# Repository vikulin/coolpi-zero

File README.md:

# GammaPi Zero - The portable FPGA development board

## What is the GammaPi Zero?

The GammaPi Zero is an FPGA development board in the popular Raspberry Pi Zero form factor inheriting Icepi Zero board. It carries a Lattice ECP5 25F, enabling powerful designs while keeping a small portable size. It also has a GPDI mini (General Purpose Display Interface, same as the one on the Pi Zero) port allowing easy digital video output.

## Why GammaPi Zero?

Currently most powerful FPGA boards on the market are expensive and bulky.

I've always wanted a low-cost portable FPGA with video output to make my own CPU, but there isn't any on the market.

The GammaPi Zero aims to fix this. Carrying a powerful ECP5 FPGA on a small Raspberry Pi Zero form factor, it is the ultimate portable solution for FPGA development. Additionally packing a GPDI mini port and 3 USB-C ports, it allows interfacing with multiple external I/O devGammas.

GammaPi Zero is for everyone: Students can use it to learn about the internals of modern processors. Gamers can use it to emulate old hardware. Programmers can use it to test their code on multiple architectures.

GammaPi Zero also has an on-board USB to JTAG converter, so no external programmers are needed.

Moreover GammaPi Zero is fully open-source, no strings attached. Learn from the design! ([OSHWA cerified FR000026](https://certification.oshwa.org/fr000026.html)).

## Features
    * Lattice ECP5U-25F-CABGA256 FPGA
    * 256 Mib SDRAM
    * DVI video output via HDMI connector
    * 50 MBPS ADC
    * 3× USB ports (1× programming/JTAG, 2× general purpose)
    * USB-JTAG programming interface
    * Mini SD card reader
    * 5× RGB LEDs
    * 2× user buttons
    * RP Zero–compatible pins and board size
    * Board dimensions: 65 × 30 mm

This powerful configuration allows the PCB to be used in numerous ways, including real time video processing, hardware AI acceleration and prototyping of ASICs. 

## Emulation

Over the course of multiple weeks, multiple emulation cores have been ported over, such as the [Oberon](https://github.com/cheyao/oberon), [Apple I](https://github.com/cheyao/apple-one) and the [Acorn Atom](https://github.com/cheyao/acorn_atom)! The GammaPi Zero allows you to take cycle accurate replicas of your favourite systems in your pocket.

## Learning

It is also supported by Icestudio (custom fork: https://github.com/cheyao/Icestudio), allowing easy access for beginners.

## Usage

Check out the `firmware` folder for example code and compilation instructions!

If you want to order this board, it uses a 1.2mm/1.6mm PCB with JLC04121H-7628 Stackup. Gerbers are in the `production` folder in the `hardware` directory.

For the PCB, the smallest component size is 0201 for 27 Ohm resistors on the USB-C datalines. But if you want only 0402 components, just delete those 0201 resistors and you will be fine.

NOTE: If you fabbed v1.1 before 01/06, the pins of the USB pullups and LED0 is different - check your gerbers.

## Contact

If there is any questions email me `vadym.vikulin _at_ gmail.com` or DM `@Cyao` on Hackclub Slack.

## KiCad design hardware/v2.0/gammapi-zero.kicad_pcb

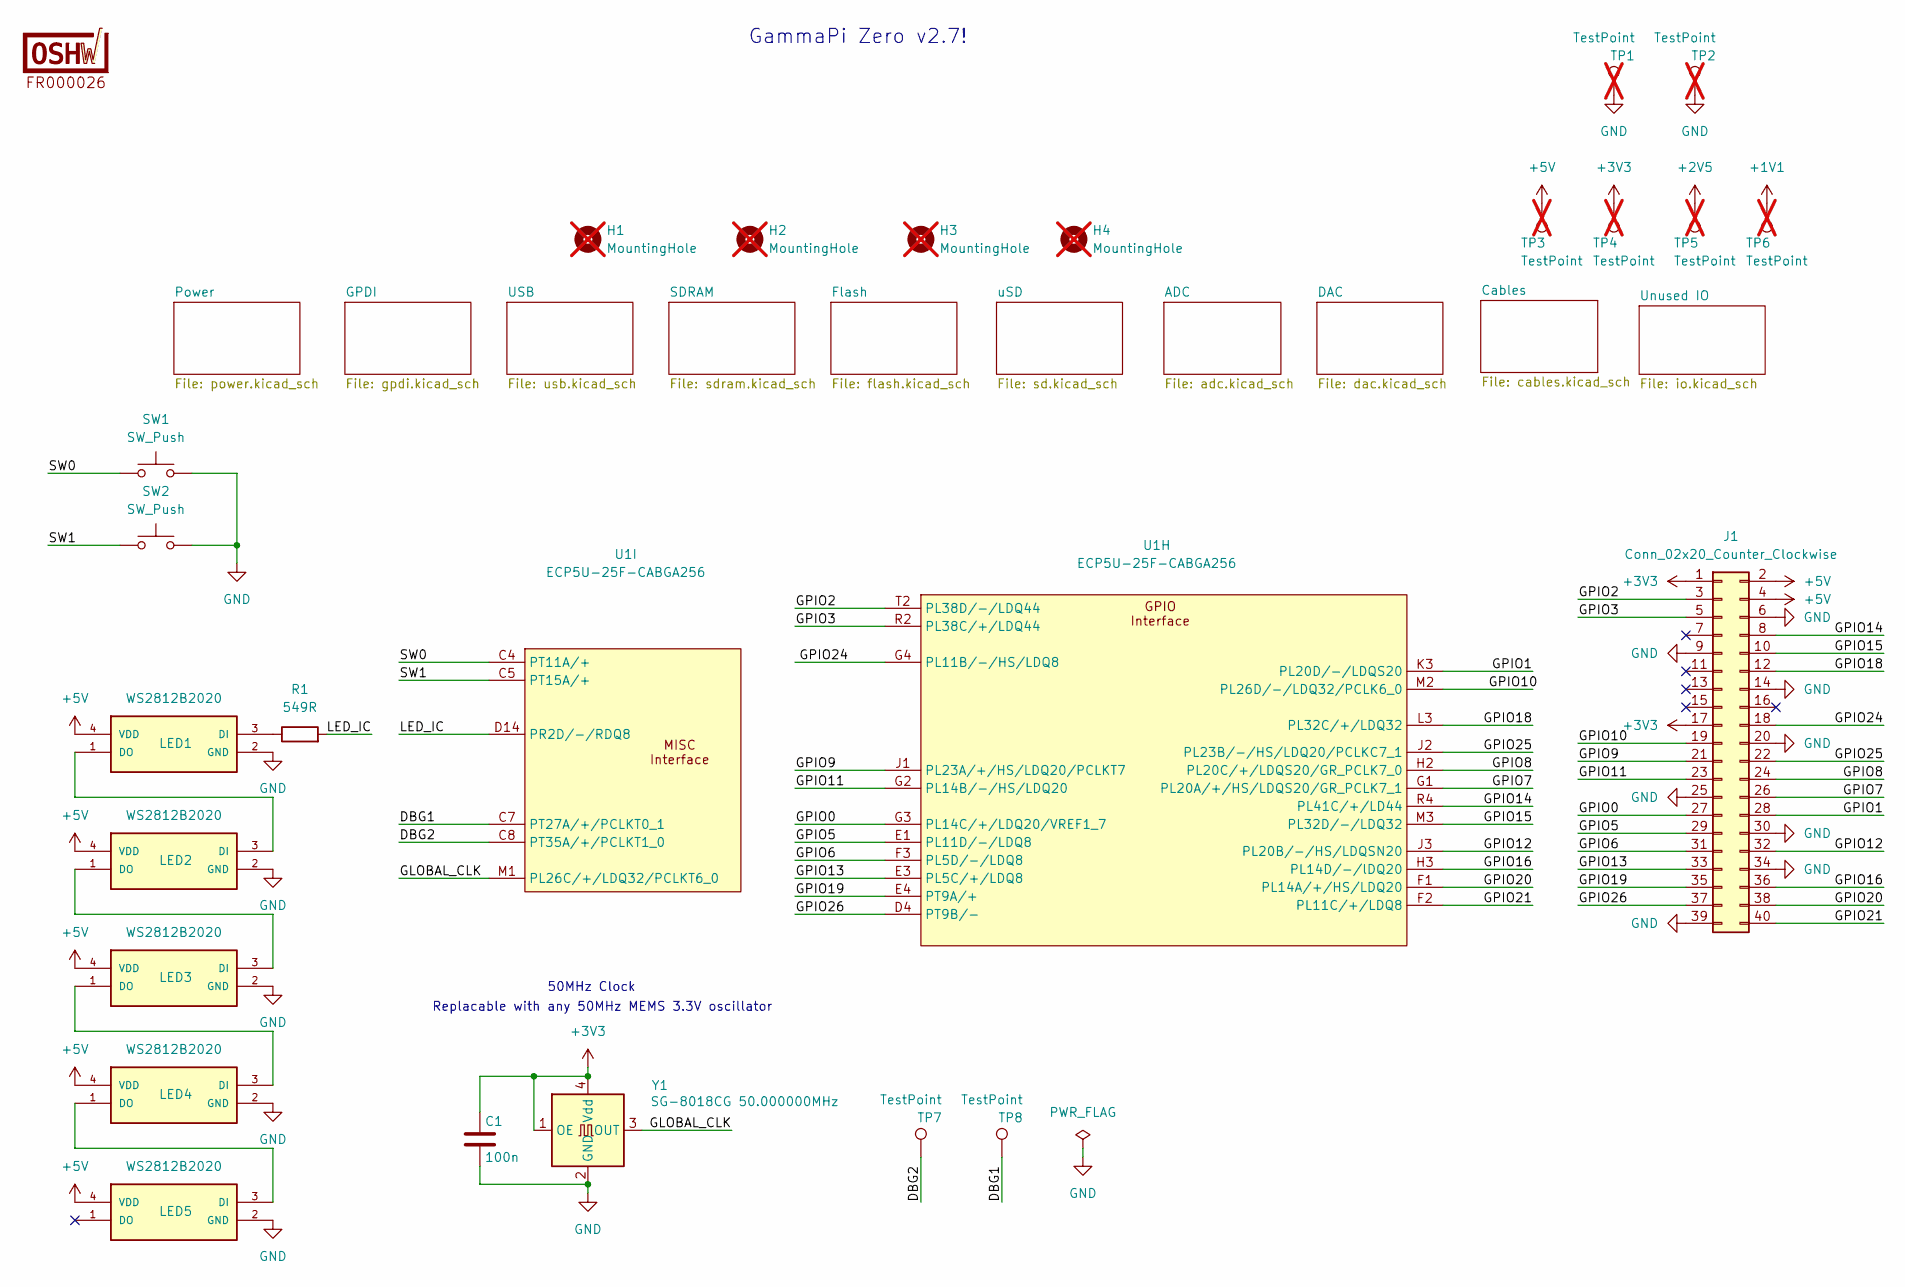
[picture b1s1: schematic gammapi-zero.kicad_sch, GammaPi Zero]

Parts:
C1: 100n; C_0402_1005Metric; Manufactuer Part Number CL05B104KB54PNC; LCSC Part # C307331
H1, H2, H3, H4: MountingHole; MountingHole_2.7mm_M2.5; not fitted
J1: Conn_02x20_Counter_Clockwise; PinHeader_2x20_P2.54mm_Vertical
LED1, LED2, LED3, LED4, LED5: WS2812B2020; LED_WS2812B2020; PARTREV V1.0; LCSC Part # C965555
LOGO1: OSHW-Certification-Mark-Logo_6x3mm_SilkScreen
R1: 549R; R_0402_1005Metric; Manufactuer Part Number 0402WGF5490TCE; LCSC Part # C474081
SW1, SW2: SW_Push; switch_button_TS-1088-AR02016; Manufactuer Part Number TS-1088-AR02016; LCSC Part # C720477
TP1, TP2, TP3, TP4, TP5, TP6: TestPoint; TestPoint_Pad_D2.0mm_Blank; not fitted
TP7, TP8: TestPoint; TestPoint_Pad_D1.0mm_Blank
U1: ECP5U-25F-CABGA256; BGA-256_14.0x14.0mm_Layout16x16_P0.8mm_Ball0.45mm_Pad0.32mm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; MANUFACTURER_PART_NUMBER LFE5U-25F-6BG256C; LCSC Part # C1521614
Y1: SG-8018CG 50.000000MHz; Oscillator_SMD_SiT_PQFN-4Pin_2.5x2.0mm; Manufactuer Part Number SG-8018CG 50.000000MHz TJHSA; LCSC Part # C390526

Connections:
+1V1: TP6.1; also elsewhere on the board
+2V5: TP5.1; also elsewhere on the board
+3V3: C1.1, J1.1, J1.17, TP4.1, Y1.1 (OE), Y1.4 (Vdd); also elsewhere on the board
+5V: J1.2, J1.4, LED1.4 (VDD), LED2.4 (VDD), LED3.4 (VDD), LED4.4 (VDD), LED5.4 (VDD), TP3.1; also elsewhere on the board
/DBG1: TP8.1, U1.C7 (PT27A/+/PCLKT0_1)
/DBG2: TP7.1, U1.C8 (PT35A/+/PCLKT1_0)
/GLOBAL_CLK: U1.M1 (PL26C/+/LDQ32/PCLKT6_0), Y1.3 (OUT)
/GPIO0: J1.27, U1.G3 (PL14C/+/LDQ20/VREF1_7)
/GPIO1: J1.28, U1.K3 (PL20D/-/LDQS20)
/GPIO2: J1.3, U1.T2 (PL38D/-/LDQ44)
/GPIO3: J1.5, U1.R2 (PL38C/+/LDQ44)
/GPIO5: J1.29, U1.E1 (PL11D/-/LDQ8)
/GPIO6: J1.31, U1.F3 (PL5D/-/LDQ8)
/GPIO7: J1.26, U1.G1 (PL20A/+/HS/LDQS20/GR_PCLK7_1)
/GPIO8: J1.24, U1.H2 (PL20C/+/LDQS20/GR_PCLK7_0)
/GPIO9: J1.21, U1.J1 (PL23A/+/HS/LDQ20/PCLKT7)
/GPIO10: J1.19, U1.M2 (PL26D/-/LDQ32/PCLK6_0)
/GPIO11: J1.23, U1.G2 (PL14B/-/HS/LDQ20)
/GPIO12: J1.32, U1.J3 (PL20B/-/HS/LDQSN20)
/GPIO13: J1.33, U1.E3 (PL5C/+/LDQ8)
/GPIO14: J1.8, U1.R4 (PL41C/+/LD44)
/GPIO15: J1.10, U1.M3 (PL32D/-/LDQ32)
/GPIO16: J1.36, U1.H3 (PL14D/-/lDQ20)
/GPIO18: J1.12, U1.L3 (PL32C/+/LDQ32)
/GPIO19: J1.35, U1.E4 (PT9A/+)
/GPIO20: J1.38, U1.F1 (PL14A/+/HS/LDQ20)
/GPIO21: J1.40, U1.F2 (PL11C/+/LDQ8)
/GPIO24: J1.18, U1.G4 (PL11B/-/HS/LDQ8)
/GPIO25: J1.22, U1.J2 (PL23B/-/HS/LDQ20/PCLKC7_1)
/GPIO26: J1.37, U1.D4 (PT9B/-)
/LED_IC: R1.2, U1.D14 (PR2D/-/RDQ8)
/SW0: SW1.1, U1.C4 (PT11A/+)
/SW1: SW2.1, U1.C5 (PT15A/+)
GND: C1.2, J1.6, J1.9, J1.14, J1.20, J1.25, J1.30, J1.34, J1.39, LED1.2 (GND), LED2.2 (GND), LED3.2 (GND), LED4.2 (GND), LED5.2 (GND), SW1.2, SW2.2, TP1.1, TP2.1, Y1.2 (GND); also elsewhere on the board
unnamed: LED1.3 (DI), R1.1
unnamed: LED1.1 (DO), LED2.3 (DI)
unnamed: LED2.1 (DO), LED3.3 (DI)
unnamed: LED3.1 (DO), LED4.3 (DI)
unnamed: LED4.1 (DO), LED5.3 (DI)

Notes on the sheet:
GammaPi Zero v2.7!
Replacable with any 50MHz MEMS 3.3V oscillator
50MHz Clock

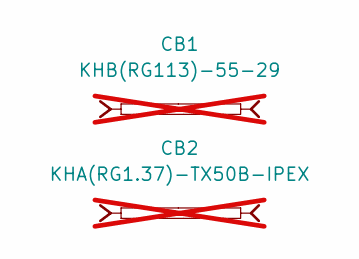
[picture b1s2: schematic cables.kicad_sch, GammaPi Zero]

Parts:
CB1: KHB(RG113)-55-29; MANUFACTURER_PART_NUMBER KHB(RG113)-55-29; LCSC Part # C454122; not fitted
CB2: KHA(RG1.37)-TX50B-IPEX; MANUFACTURER_PART_NUMBER KHA(RG1.37)-TX50B-IPEX; LCSC Part # C7541884; not fitted

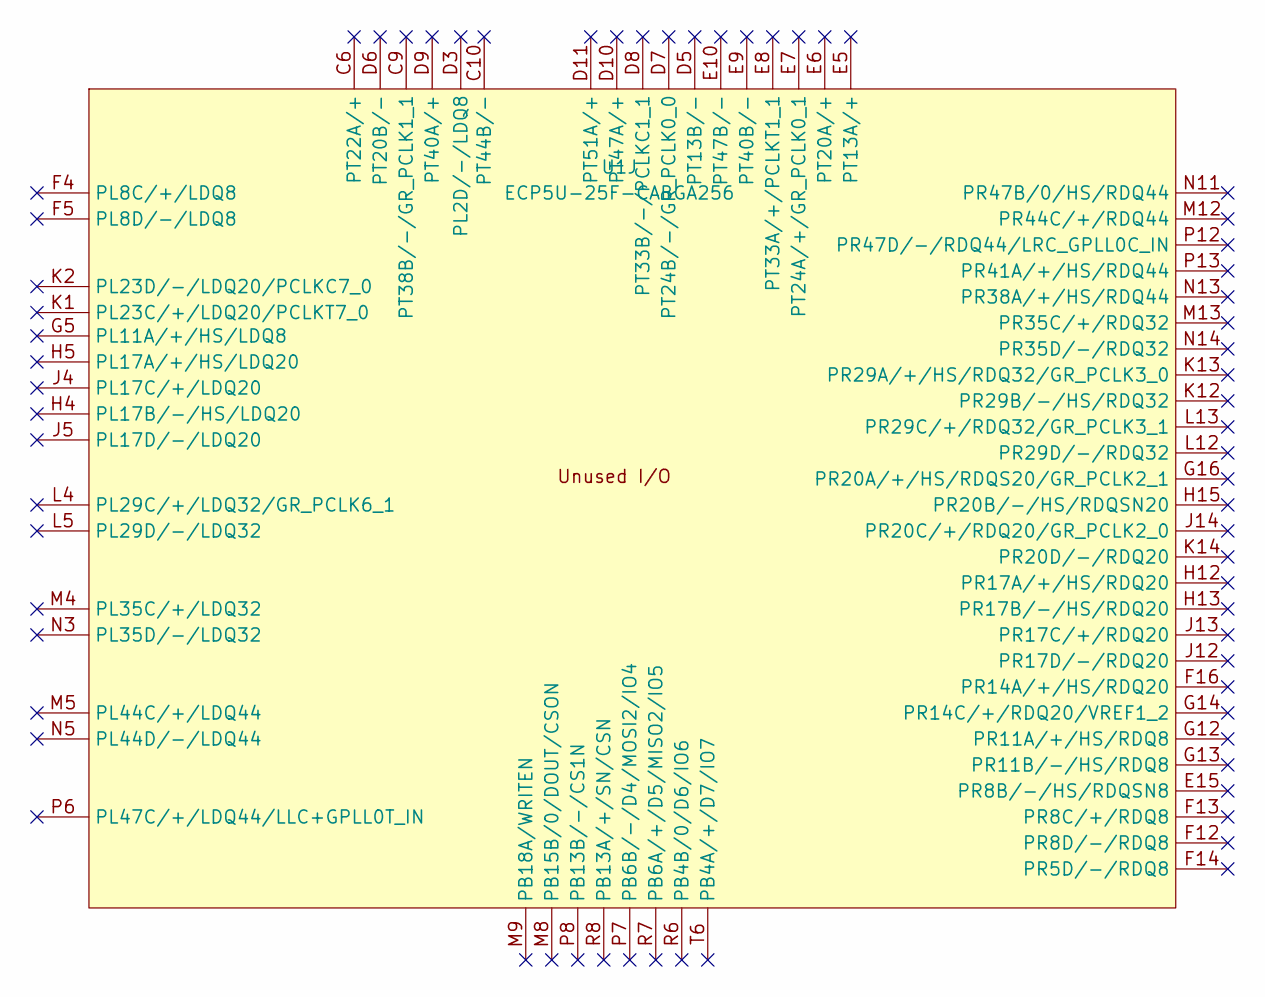
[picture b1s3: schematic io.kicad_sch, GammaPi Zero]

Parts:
U1: ECP5U-25F-CABGA256; BGA-256_14.0x14.0mm_Layout16x16_P0.8mm_Ball0.45mm_Pad0.32mm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; MANUFACTURER_PART_NUMBER LFE5U-25F-6BG256C; LCSC Part # C1521614

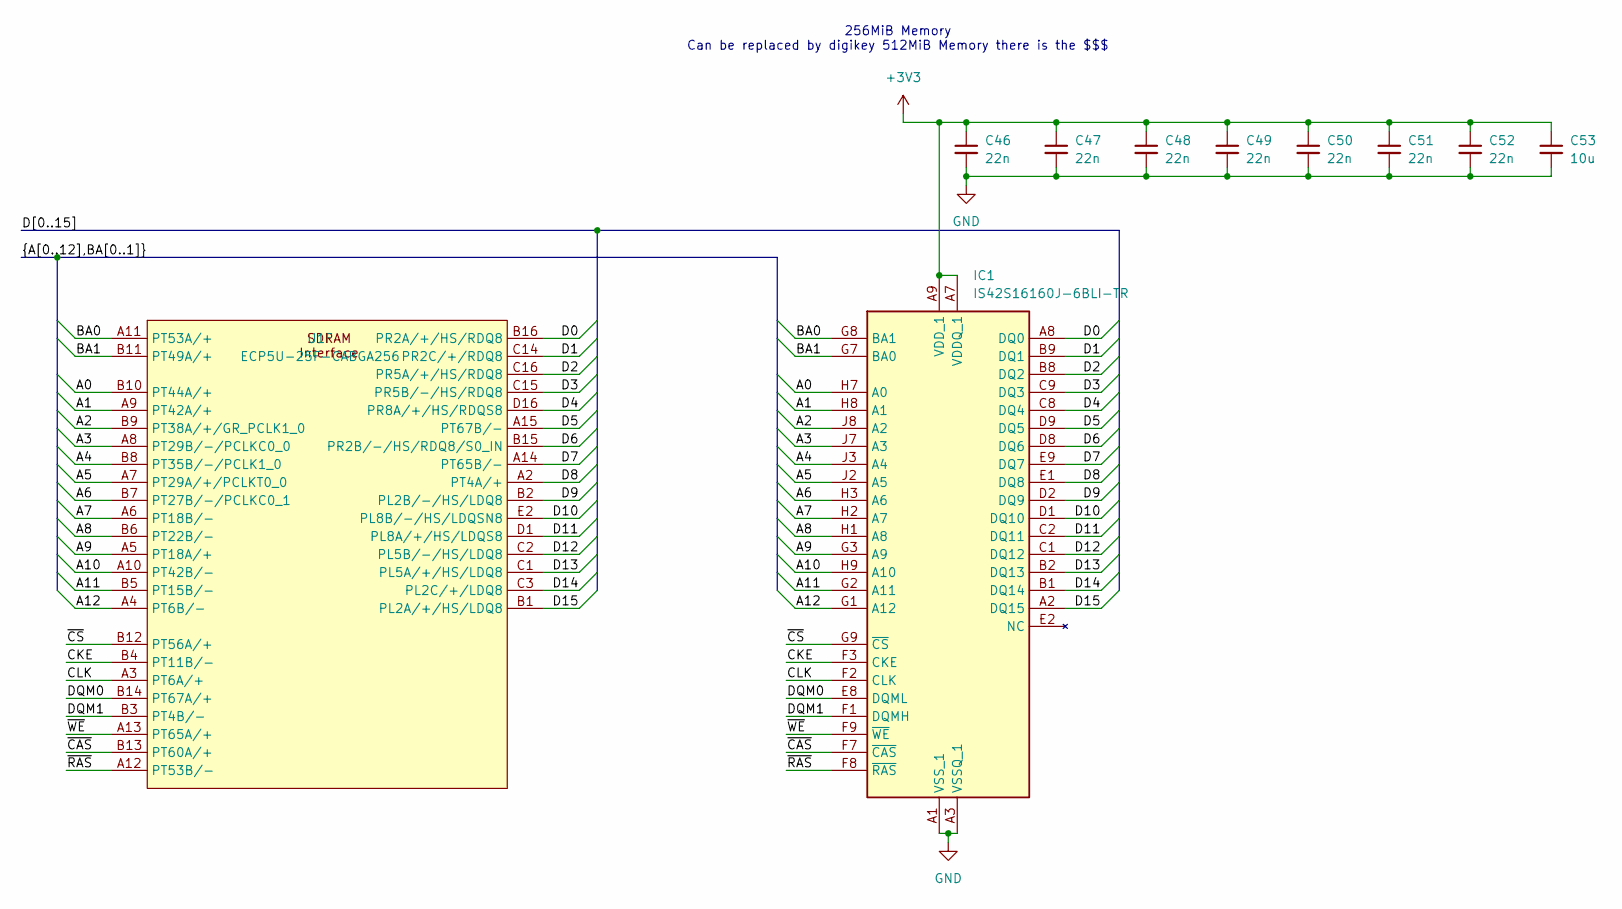
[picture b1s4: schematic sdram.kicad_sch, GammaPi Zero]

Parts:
C46, C47, C48, C49, C50, C51, C52: 22n; C_0402_1005Metric; Manufactuer Part Number 0603B223K500NT; LCSC Part # C1532
C53: 10u; C_0603_1608Metric; Manufactuer Part Number CL10A106KP8NNNC; LCSC Part # C19702
IC1: IS42S16160J-6BLI-TR; BGA54C80P9X9_800X800X120; Mouser Part Number 870-42S16160J6BLI
U1: ECP5U-25F-CABGA256; BGA-256_14.0x14.0mm_Layout16x16_P0.8mm_Ball0.45mm_Pad0.32mm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; MANUFACTURER_PART_NUMBER LFE5U-25F-6BG256C; LCSC Part # C1521614

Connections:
+3V3: C46.1, C47.1, C48.1, C49.1, C50.1, C51.1, C52.1, C53.1, IC1.A7 (VDDQ_1), IC1.A9 (VDD_1), IC1.B3 (VDDQ_2), IC1.C7 (VDDQ_3), IC1.D3 (VDDQ_4), IC1.E7 (VDD_2), IC1.J9 (VDD_3); also elsewhere on the board
/SDRAM/A0: IC1.H7 (A0), U1.B10 (PT44A/+)
/SDRAM/A1: IC1.H8 (A1), U1.A9 (PT42A/+)
/SDRAM/A2: IC1.J8 (A2), U1.B9 (PT38A/+/GR_PCLK1_0)
/SDRAM/A3: IC1.J7 (A3), U1.A8 (PT29B/-/PCLKC0_0)
/SDRAM/A4: IC1.J3 (A4), U1.B8 (PT35B/-/PCLK1_0)
/SDRAM/A5: IC1.J2 (A5), U1.A7 (PT29A/+/PCLKT0_0)
/SDRAM/A6: IC1.H3 (A6), U1.B7 (PT27B/-/PCLKC0_1)
/SDRAM/A7: IC1.H2 (A7), U1.A6 (PT18B/-)
/SDRAM/A8: IC1.H1 (A8), U1.B6 (PT22B/-)
/SDRAM/A9: IC1.G3 (A9), U1.A5 (PT18A/+)
/SDRAM/A10: IC1.H9 (A10), U1.A10 (PT42B/-)
/SDRAM/A11: IC1.G2 (A11), U1.B5 (PT15B/-)
/SDRAM/A12: IC1.G1 (A12), U1.A4 (PT6B/-)
/SDRAM/BA0: IC1.G8 (BA1), U1.A11 (PT53A/+)
/SDRAM/BA1: IC1.G7 (BA0), U1.B11 (PT49A/+)
/SDRAM/CKE: IC1.F3 (CKE), U1.B4 (PT11B/-)
/SDRAM/CLK: IC1.F2 (CLK), U1.A3 (PT6A/+)
/SDRAM/D0: IC1.A8 (DQ0), U1.B16 (PR2A/+/HS/RDQ8)
/SDRAM/D1: IC1.B9 (DQ1), U1.C14 (PR2C/+/RDQ8)
/SDRAM/D2: IC1.B8 (DQ2), U1.C16 (PR5A/+/HS/RDQ8)
/SDRAM/D3: IC1.C9 (DQ3), U1.C15 (PR5B/-/HS/RDQ8)
/SDRAM/D4: IC1.C8 (DQ4), U1.D16 (PR8A/+/HS/RDQS8)
/SDRAM/D5: IC1.D9 (DQ5), U1.A15 (PT67B/-)
/SDRAM/D6: IC1.D8 (DQ6), U1.B15 (PR2B/-/HS/RDQ8/S0_IN)
/SDRAM/D7: IC1.E9 (DQ7), U1.A14 (PT65B/-)
/SDRAM/D8: IC1.E1 (DQ8), U1.A2 (PT4A/+)
/SDRAM/D9: IC1.D2 (DQ9), U1.B2 (PL2B/-/HS/LDQ8)
/SDRAM/D10: IC1.D1 (DQ10), U1.E2 (PL8B/-/HS/LDQSN8)
/SDRAM/D11: IC1.C2 (DQ11), U1.D1 (PL8A/+/HS/LDQS8)
/SDRAM/D12: IC1.C1 (DQ12), U1.C2 (PL5B/-/HS/LDQ8)
/SDRAM/D13: IC1.B2 (DQ13), U1.C1 (PL5A/+/HS/LDQ8)
/SDRAM/D14: IC1.B1 (DQ14), U1.C3 (PL2C/+/LDQ8)
/SDRAM/D15: IC1.A2 (DQ15), U1.B1 (PL2A/+/HS/LDQ8)
/SDRAM/DQM0: IC1.E8 (DQML), U1.B14 (PT67A/+)
/SDRAM/DQM1: IC1.F1 (DQMH), U1.B3 (PT4B/-)
/SDRAM/~CAS: IC1.F7 (~CAS), U1.B13 (PT60A/+)
/SDRAM/~CS: IC1.G9 (~CS), U1.B12 (PT56A/+)
/SDRAM/~RAS: IC1.F8 (~RAS), U1.A12 (PT53B/-)
/SDRAM/~WE: IC1.F9 (~WE), U1.A13 (PT65A/+)
GND: C46.2, C47.2, C48.2, C49.2, C50.2, C51.2, C52.2, C53.2, IC1.A1 (VSS_1), IC1.A3 (VSSQ_1), IC1.B7 (VSSQ_2), IC1.C3 (VSSQ_3), IC1.D7 (VSSQ_4), IC1.E3 (VSS_2), IC1.J1 (VSS_3); also elsewhere on the board

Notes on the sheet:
256MiB Memory Can be replaced by digikey 512MiB Memory there is the $$$

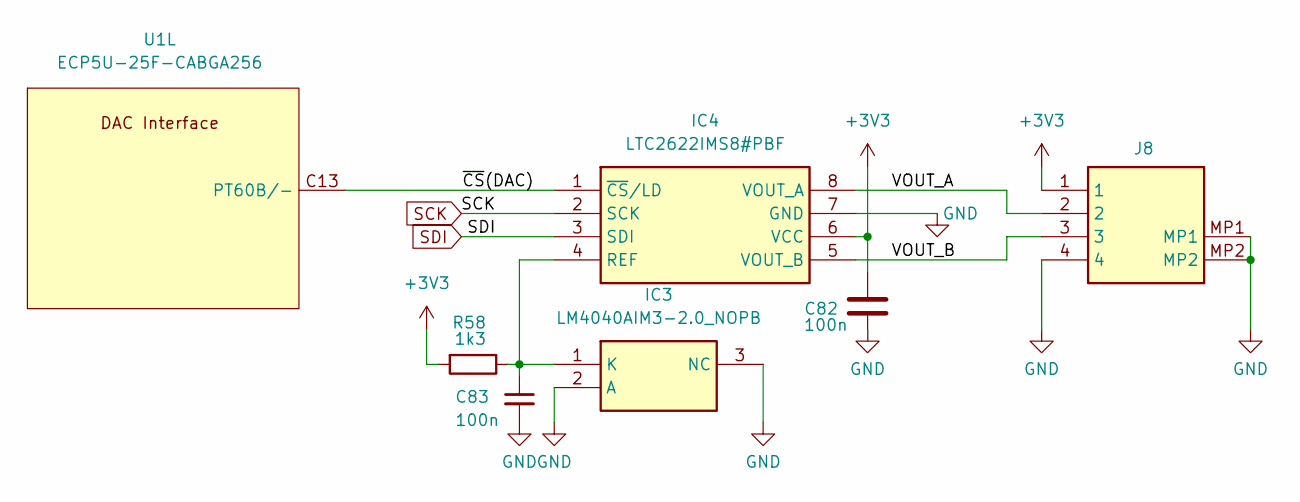
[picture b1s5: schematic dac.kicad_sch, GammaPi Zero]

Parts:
C82, C83: 100n; C_0402_1005Metric; Manufactuer Part Number CL05B104KB54PNC; LCSC Part # C307331
IC3: LM4040AIM3-2.0_NOPB; SOT95P237X95-3N; Mouser Part Number 926-LM4040AIM320NOPB
IC4: LTC2622IMS8#PBF; SOP65P490X110-8N; Mouser Part Number 584-LTC2622IMS8#PBF
J8: GT-A1201WRS-104B1101; BM04BACHSSAGANTFLFSN; Manufacturer_Part_Number GT-A1201WRS-104B1101; LCSC Part # C22384775
R58: 1k3; R_0402_1005Metric; Manufactuer Part Number 0402WGF1301TCE; LCSC Part # C25866
U1: ECP5U-25F-CABGA256; BGA-256_14.0x14.0mm_Layout16x16_P0.8mm_Ball0.45mm_Pad0.32mm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; MANUFACTURER_PART_NUMBER LFE5U-25F-6BG256C; LCSC Part # C1521614

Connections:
+3V3: C82.1, IC4.6 (VCC), J8.1, R58.2; also elsewhere on the board
/DAC/VOUT_A: IC4.8 (VOUT_A), J8.2
/DAC/VOUT_B: IC4.5 (VOUT_B), J8.3
/DAC/~CS(DAC): IC4.1 (~CS/LD), U1.C13 (PT60B/-)
GND: C82.2, C83.2, IC3.2 (A), IC3.3 (NC), IC4.7 (GND), J8.4, J8.MP1, J8.MP2; also elsewhere on the board
unnamed: C83.1, IC3.1 (K), IC4.4 (REF), R58.1
SCK: IC4.2 (SCK); also elsewhere on the board
SDI: IC4.3 (SDI); also elsewhere on the board

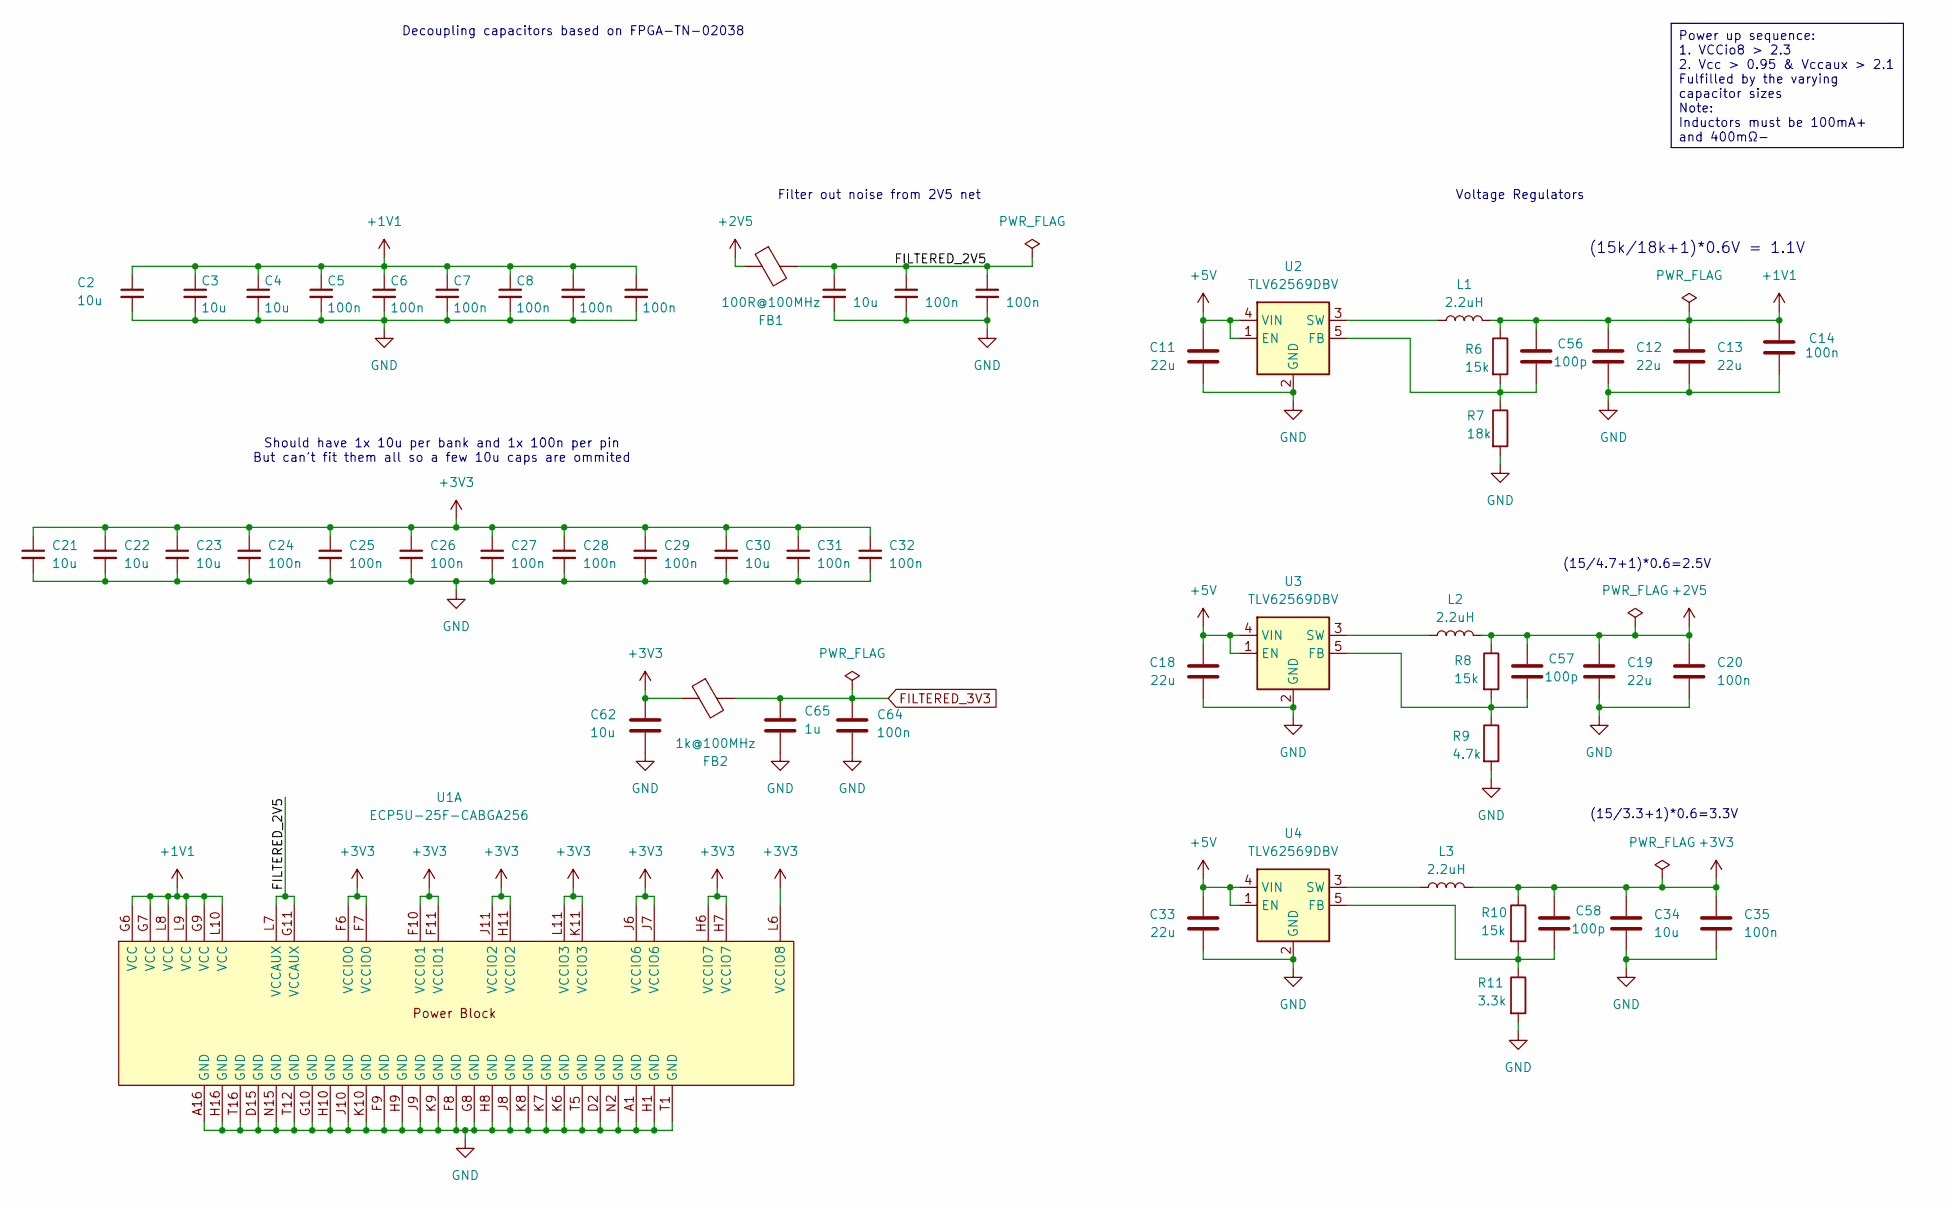
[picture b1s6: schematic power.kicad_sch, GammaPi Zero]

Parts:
C2, C62: 10u; C_0402_1005Metric; Manufactuer Part Number CL05A106MP5NUNC; LCSC Part # C315248
C3, C4, C15, C21, C22, C23, C30, C34: 10u; C_0603_1608Metric; Manufactuer Part Number CL10A106KP8NNNC; LCSC Part # C19702
C5, C6, C7, C8, C9, C10, C14, C16, C17, C20, C24, C25, C26, C27, C28, C29, C31, C32, C35, C64: 100n; C_0402_1005Metric; Manufactuer Part Number CL05B104KB54PNC; LCSC Part # C307331
C11, C12, C13, C18, C19, C33: 22u; C_0603_1608Metric; Manufactuer Part Number CL10A226MQ8NRNC; LCSC Part # C59461
C56, C57, C58: 100p; C_0402_1005Metric; Manufactuer Part Number CL05C101JB5NNNC; LCSC Part # C26409
C65: 1u; C_0402_1005Metric; Manufactuer Part Number CC0402KRX5R6BB105; LCSC Part # C106254
FB1: 100R@100MHz; L_0805_2012Metric; Manufactuer Part Number CBG201209U101T; LCSC Part # C74480
FB2: 1k@100MHz; L_0603_1608Metric; Manufactuer Part Number BLM18AG102SN1D; LCSC Part # C85824
L1, L2, L3: 2.2uH; L_0805_2012Metric; Manufactuer Part Number TDK MLP2012S2R2MT0S1; LCSC Part # C107322
R6, R8, R10: 15k; R_0402_1005Metric; Manufactuer Part Number 0402WGF1502TCE; LCSC Part # C25756
R7: 18k; R_0402_1005Metric; Manufactuer Part Number 0402WGF1802TCE; LCSC Part # C25762
R9: 4.7k; R_0402_1005Metric; Manufactuer Part Number 0402WGF4701TCE; LCSC Part # C25900
R11: 3.3k; R_0402_1005Metric; Manufactuer Part Number 0402WGF3301TCE; LCSC Part # C25890
U1: ECP5U-25F-CABGA256; BGA-256_14.0x14.0mm_Layout16x16_P0.8mm_Ball0.45mm_Pad0.32mm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; MANUFACTURER_PART_NUMBER LFE5U-25F-6BG256C; LCSC Part # C1521614
U2, U3, U4: TLV62569DBV; SOT-23-5; Manufactuer Part Number TLV62569DBVR; LCSC Part # C141836

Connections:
+1V1: C2.1, C3.1, C4.1, C5.1, C6.1, C7.1, C8.1, C9.1, C10.1, C12.1, C13.1, C14.1, C56.1, L1.2, R6.1, U1.G6 (VCC), U1.G7 (VCC), U1.G9 (VCC), U1.L8 (VCC), U1.L9 (VCC), U1.L10 (VCC); also elsewhere on the board
+2V5: C19.1, C20.1, C57.1, FB1.1, L2.2, R8.1; also elsewhere on the board
+3V3: C21.1, C22.1, C23.1, C24.1, C25.1, C26.1, C27.1, C28.1, C29.1, C30.1, C31.1, C32.1, C34.1, C35.1, C58.1, C62.1, FB2.1, L3.2, R10.1, U1.F6 (VCCIO0), U1.F7 (VCCIO0), U1.F10 (VCCIO1), U1.F11 (VCCIO1), U1.H6 (VCCIO7), U1.H7 (VCCIO7), U1.H11 (VCCIO2), U1.J6 (VCCIO6), U1.J7 (VCCIO6), U1.J11 (VCCIO2), U1.K11 (VCCIO3), U1.L6 (VCCIO8), U1.L11 (VCCIO3); also elsewhere on the board
+5V: C11.1, C18.1, C33.1, U2.1 (EN), U2.4 (VIN), U3.1 (EN), U3.4 (VIN), U4.1 (EN), U4.4 (VIN); also elsewhere on the board
/Power/FILTERED_2V5: C15.1, C16.1, C17.1, FB1.2, U1.G11 (VCCAUX), U1.L7 (VCCAUX)
FILTERED_3V3: C64.2, C65.1, FB2.2; also elsewhere on the board
GND: C2.2, C3.2, C4.2, C5.2, C6.2, C7.2, C8.2, C9.2, C10.2, C11.2, C12.2, C13.2, C14.2, C15.2, C16.2, C17.2, C18.2, C19.2, C20.2, C21.2, C22.2, C23.2, C24.2, C25.2, C26.2, C27.2, C28.2, C29.2, C30.2, C31.2, C32.2, C33.2, C34.2, C35.2, C62.2, C64.1, C65.2, R7.2, R9.2, R11.2, U1.A1 (GND), U1.A16 (GND), U1.D2 (GND), U1.D15 (GND), U1.F8 (GND), U1.F9 (GND), U1.G8 (GND), U1.G10 (GND), U1.H1 (GND), U1.H8 (GND), U1.H9 (GND), U1.H10 (GND), U1.H16 (GND), U1.J8 (GND), U1.J9 (GND), U1.J10 (GND), U1.K6 (GND), U1.K7 (GND), U1.K8 (GND), U1.K9 (GND), U1.K10 (GND), U1.N2 (GND), U1.N15 (GND), U1.T1 (GND), U1.T5 (GND), U1.T12 (GND), U1.T16 (GND), U2.2 (GND), U3.2 (GND), U4.2 (GND); also elsewhere on the board
unnamed: C56.2, R6.2, R7.1, U2.5 (FB)
unnamed: L1.1, U2.3 (SW)
unnamed: C57.2, R8.2, R9.1, U3.5 (FB)
unnamed: L2.1, U3.3 (SW)
unnamed: C58.2, R10.2, R11.1, U4.5 (FB)
unnamed: L3.1, U4.3 (SW)

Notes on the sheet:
Decoupling capacitors based on FPGA-TN-02038
Filter out noise from 2V5 net
(15/4.7+1)*0.6=2.5V
Should have 1x 10u per bank and 1x 100n per pin But can't fit them all so a few 10u caps are ommited
(15/3.3+1)*0.6=3.3V
(15k/18k+1)*0.6V = 1.1V
Voltage Regulators
Power up sequence: 1. VCCio8 > 2.3 2. Vcc > 0.95 & Vccaux > 2.1 Fulfilled by the varying capacitor sizes Note: Inductors must be 100mA+ and 400mΩ-

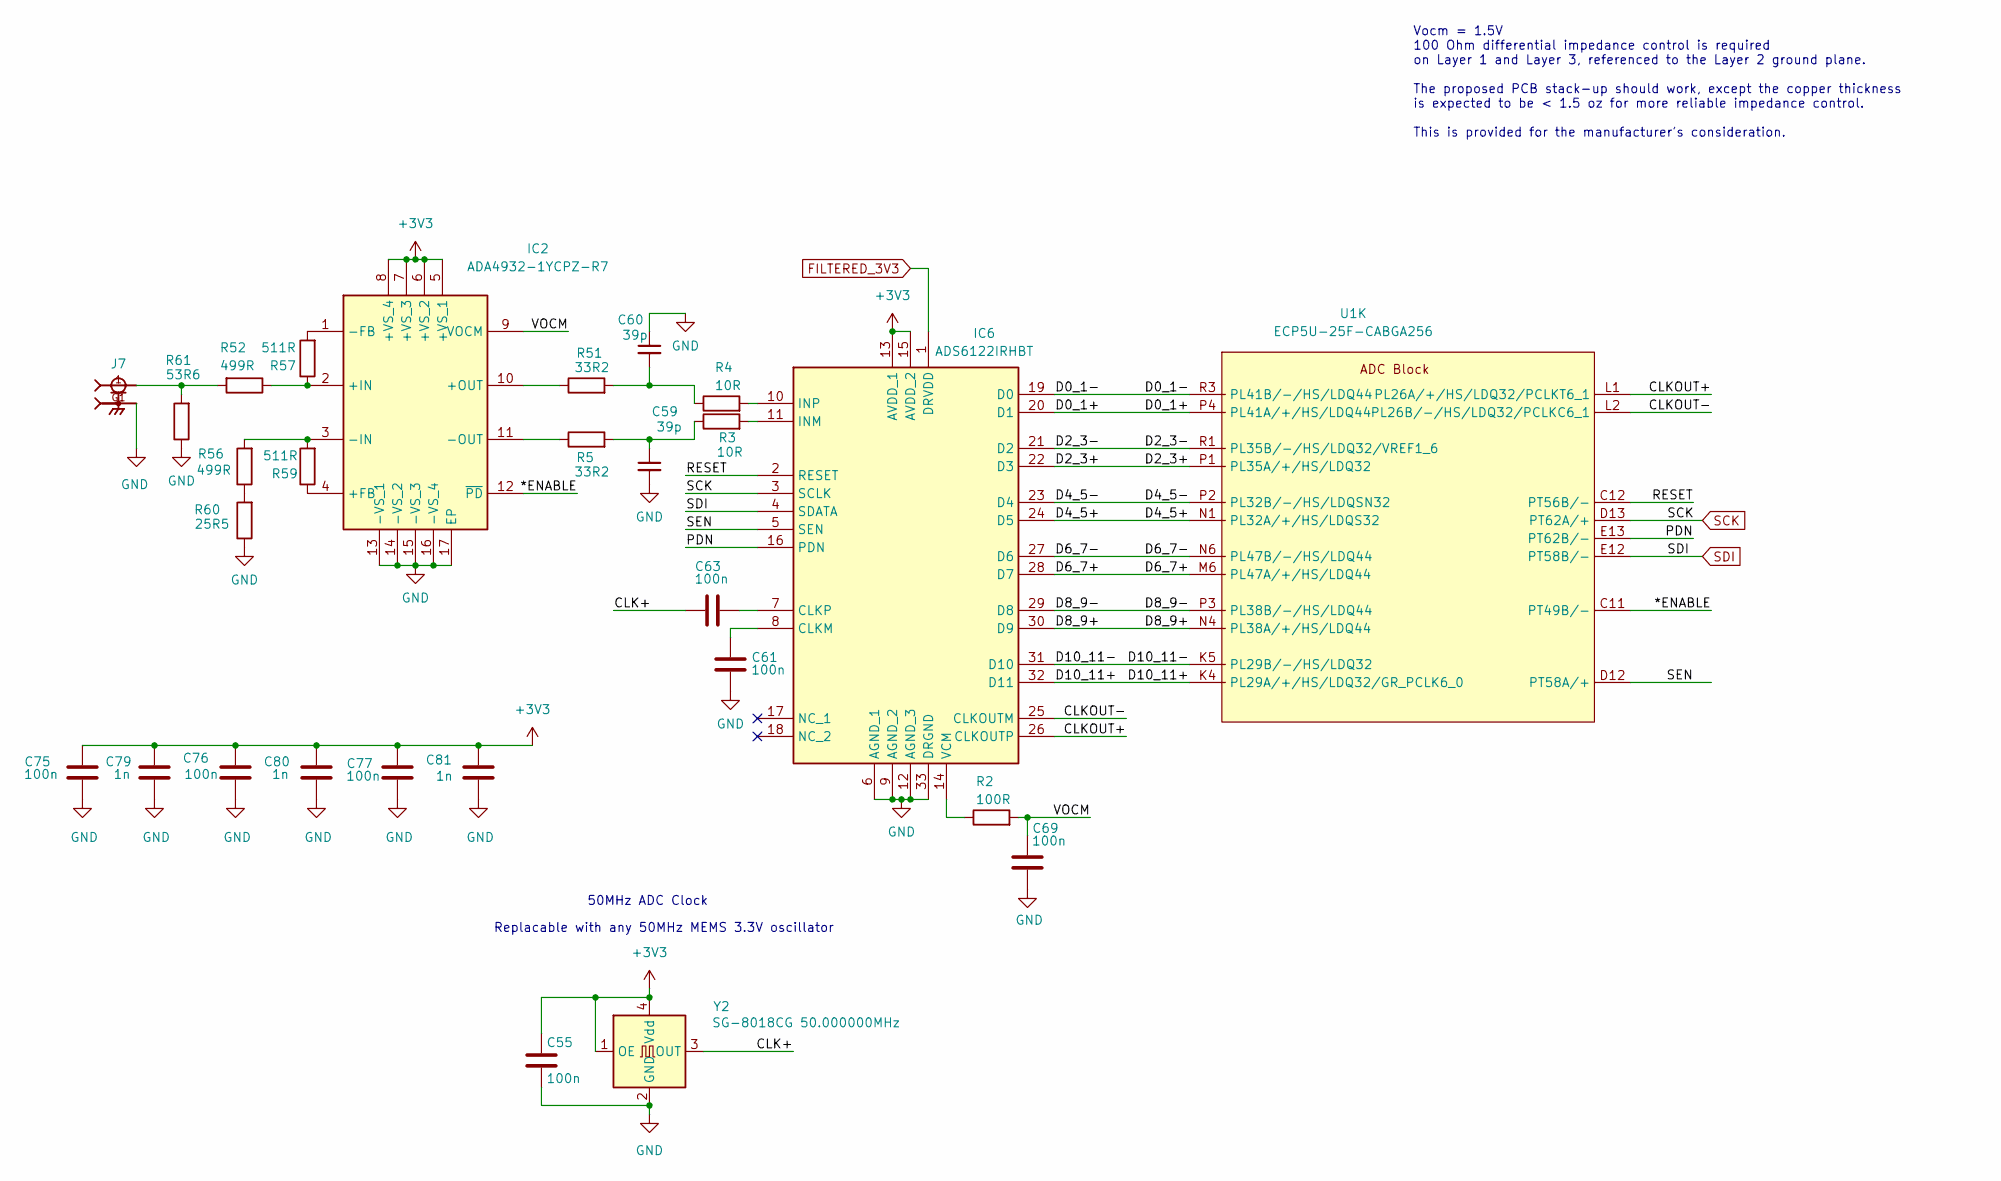
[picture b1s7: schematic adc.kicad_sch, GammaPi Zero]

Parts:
C55, C61, C63, C69, C75, C76, C77: 100n; C_0402_1005Metric; Manufactuer Part Number CL05B104KB54PNC; LCSC Part # C307331
C59, C60: 39p; C_0402_1005Metric; Manufactuer Part Number CL05C390JB5NNNC; LCSC Part # C86288
C79, C80, C81: 1n; C_0402_1005Metric; Manufactuer Part Number CL05B102KB5NNNC; LCSC Part # C14442
IC2: ADA4932-1YCPZ-R7; QFN50P300X300X80-17N-D; Mouser Part Number 584-ADA4932-1YCPZ-R7
IC6: ADS6122IRHBT; QFN50P500X500X100-33N-D; Mouser Part Number 595-ADS6122IRHBT
J7: RSP-122811-01; SAMTEC_RSP-122811-01; PARTREV H; LCSC Part # C2938932
R2: 100R; R_0402_1005Metric; Manufactuer Part Number 0402WGF1000TCE; LCSC Part # C25076
R3, R4: 10R; R_0402_1005Metric; Manufactuer Part Number 0402WGF100JTCE; LCSC Part # C25077
R5, R51: 33R2; R_0402_1005Metric; Manufactuer Part Number 0402WGF332JTCE; LCSC Part # C25106
R52, R56: 499R; R_0402_1005Metric; Manufactuer Part Number 0402WGF4990TCE; LCSC Part # C4125
R57, R59: 511R; R_0402_1005Metric; Manufactuer Part Number 0402WGF5110TCE; LCSC Part # C25124
R60: 25R5; R_0402_1005Metric; Manufactuer Part Number 0402WGF255JTCE; LCSC Part # C129579
R61: 53R6; R_0402_1005Metric; Manufactuer Part Number 0402WGF536JTCE; LCSC Part # C423156
U1: ECP5U-25F-CABGA256; BGA-256_14.0x14.0mm_Layout16x16_P0.8mm_Ball0.45mm_Pad0.32mm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; MANUFACTURER_PART_NUMBER LFE5U-25F-6BG256C; LCSC Part # C1521614
Y2: SG-8018CG 50.000000MHz; Oscillator_SMD_SiT_PQFN-4Pin_2.5x2.0mm; Manufactuer Part Number SG-8018CG 50.000000MHz TJHSA; LCSC Part # C390526

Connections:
+3V3: C55.1, C75.1, C76.1, C77.1, C79.1, C80.1, C81.1, IC2.5 (+VS_1), IC2.6 (+VS_2), IC2.7 (+VS_3), IC2.8 (+VS_4), IC6.13 (AVDD_1), IC6.15 (AVDD_2), Y2.1 (OE), Y2.4 (Vdd); also elsewhere on the board
/ADC/*ENABLE: IC2.12 (~PD), U1.C11 (PT49B/-)
/ADC/CLK+: C63.1, Y2.3 (OUT)
/ADC/CLKOUT+: IC6.26 (CLKOUTP), U1.L1 (PL26A/+/HS/LDQ32/PCLKT6_1)
/ADC/CLKOUT-: IC6.25 (CLKOUTM), U1.L2 (PL26B/-/HS/LDQ32/PCLKC6_1)
/ADC/D0_1+: IC6.20 (D1), U1.P4 (PL41A/+/HS/LDQ44)
/ADC/D0_1-: IC6.19 (D0), U1.R3 (PL41B/-/HS/LDQ44)
/ADC/D2_3+: IC6.22 (D3), U1.P1 (PL35A/+/HS/LDQ32)
/ADC/D2_3-: IC6.21 (D2), U1.R1 (PL35B/-/HS/LDQ32/VREF1_6)
/ADC/D4_5+: IC6.24 (D5), U1.N1 (PL32A/+/HS/LDQS32)
/ADC/D4_5-: IC6.23 (D4), U1.P2 (PL32B/-/HS/LDQSN32)
/ADC/D6_7+: IC6.28 (D7), U1.M6 (PL47A/+/HS/LDQ44)
/ADC/D6_7-: IC6.27 (D6), U1.N6 (PL47B/-/HS/LDQ44)
/ADC/D8_9+: IC6.30 (D9), U1.N4 (PL38A/+/HS/LDQ44)
/ADC/D8_9-: IC6.29 (D8), U1.P3 (PL38B/-/HS/LDQ44)
/ADC/D10_11+: IC6.32 (D11), U1.K4 (PL29A/+/HS/LDQ32/GR_PCLK6_0)
/ADC/D10_11-: IC6.31 (D10), U1.K5 (PL29B/-/HS/LDQ32)
/ADC/PDN: IC6.16 (PDN), U1.E13 (PT62B/-)
/ADC/RESET: IC6.2 (RESET), U1.C12 (PT56B/-)
/ADC/SEN: IC6.5 (SEN), U1.D12 (PT58A/+)
/ADC/VOCM: C69.1, IC2.9 (VOCM), R2.2
FILTERED_3V3: IC6.1 (DRVDD); also elsewhere on the board
GND: C55.2, C59.2, C60.1, C61.2, C69.2, C75.2, C76.2, C77.2, C79.2, C80.2, C81.2, IC2.13 (-VS_1), IC2.14 (-VS_2), IC2.15 (-VS_3), IC2.16 (-VS_4), IC2.17 (EP), IC6.6 (AGND_1), IC6.9 (AGND_2), IC6.12 (AGND_3), IC6.33 (DRGND), J7.G1, J7.G2, R60.1, R61.1, Y2.2 (GND); also elsewhere on the board
unnamed: C59.1, R3.1, R5.2
unnamed: C60.2, R4.1, R51.2
unnamed: IC2.4 (+FB), R59.1
unnamed: IC2.2 (+IN), R52.1, R57.1
unnamed: IC2.10 (+OUT), R51.1
unnamed: IC2.1 (-FB), R57.2
unnamed: IC2.3 (-IN), R56.2, R59.2
unnamed: IC2.11 (-OUT), R5.1
unnamed: C61.1, IC6.8 (CLKM)
unnamed: C63.2, IC6.7 (CLKP)
unnamed: IC6.11 (INM), R3.2
unnamed: IC6.10 (INP), R4.2
unnamed: IC6.14 (VCM), R2.1
unnamed: J7.1, R52.2, R61.2
unnamed: R56.1, R60.2
SCK: IC6.3 (SCLK), U1.D13 (PT62A/+); also elsewhere on the board
SDI: IC6.4 (SDATA), U1.E12 (PT58B/-); also elsewhere on the board

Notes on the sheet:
Vocm = 1.5V 100 Ohm differential impedance control is required on Layer 1 and Layer 3, referenced to the Layer 2 ground plane. The proposed PCB stack-up should work, except the copper thickness is expected to be < 1.5 oz for more reliable impedance control. This is provided for the manufacturer's c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
50MHz ADC Clock
Replacable with any 50MHz MEMS 3.3V oscillator

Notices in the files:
hardware/v1.3/sdram.kicad_sch:
License: Solderpad
